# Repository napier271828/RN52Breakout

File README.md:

# RN52Breakout
Compact Breakout for Microchip RN-52I

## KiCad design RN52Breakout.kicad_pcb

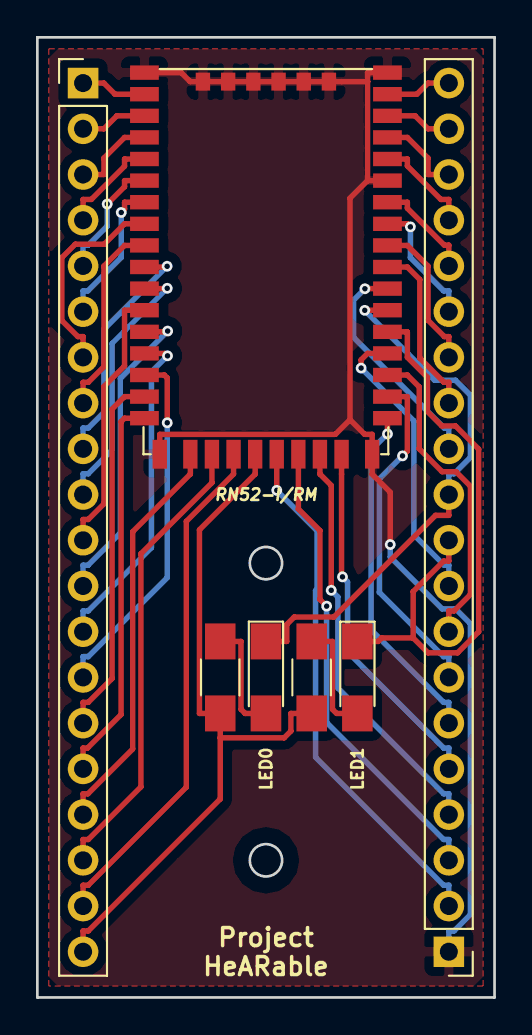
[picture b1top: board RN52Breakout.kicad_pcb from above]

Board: 2 copper layers, 25.4 x 53.3 mm, 7 parts (0 on the bottom side), 42 nets.

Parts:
BT1: RN52-I/RM; LGA50-1.0-26X13.5MM
J1, J2: HEADER_20; Pin_Header_Straight_1x20_Pitch2.54mm
LED0, LED1: LED; LED_1206_HandSoldering
R1, R2: 330; R_1206_HandSoldering

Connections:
LED0: BT1.33, J2.11, LED0.1
LED1: BT1.32, J2.10, LED1.1
unnamed: BT1.1, BT1.18, BT1.27, BT1.39, BT1.44, BT1.45, BT1.46, BT1.47, BT1.48, BT1.49, BT1.50, J2.1
unnamed: BT1.2, J1.1
unnamed: BT1.3, J1.2
unnamed: BT1.4, J1.3
unnamed: BT1.5, J1.4
unnamed: BT1.6, J1.5
unnamed: BT1.7, J1.6
unnamed: BT1.8, J1.7
unnamed: BT1.9, J1.8
unnamed: BT1.10, J1.9
unnamed: BT1.11, J1.10
unnamed: BT1.12, J1.11
unnamed: BT1.13, J1.12
unnamed: BT1.14, J1.13
unnamed: BT1.15, J1.14
unnamed: BT1.16, J1.15
unnamed: BT1.17, J1.16
unnamed: BT1.19, J1.17
unnamed: BT1.20, J1.18
unnamed: BT1.21, J1.19
unnamed: BT1.22, J1.20, R1.1, R2.1
unnamed: BT1.23, J2.2
unnamed: BT1.24, J2.3
unnamed: BT1.25, J2.4
unnamed: BT1.26, J2.5
unnamed: BT1.28, J2.6
unnamed: BT1.29, J2.7
unnamed: BT1.30, J2.8
unnamed: BT1.31, J2.9
unnamed: BT1.34, J2.12
unnamed: BT1.35, J2.13
unnamed: BT1.36, J2.14
unnamed: BT1.37, J2.15
unnamed: BT1.38, J2.16
unnamed: BT1.40, J2.17
unnamed: BT1.41, J2.18
unnamed: BT1.42, J2.19
unnamed: BT1.43, J2.20
unnamed: LED0.2, R1.2
unnamed: LED1.2, R2.2

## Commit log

2018-05-07 Create LICENSE
2018-05-07 add pcb overview to readme
